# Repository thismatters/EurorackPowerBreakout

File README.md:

Power Breakout
---------------

Ever wanted to prototype a circuit for your Eurorack but didn't have a benchtop power supply for testing? Worry no more! With this small crouton (and an extra long ribbon cable) you can plug your breadboard into your rack as though it were a module.

The crouton includes twin LEDs to show that the 12 volt rails are hot, load smoothing capactiors and resistors. Use a jumper to select between 5 volts and ground on the +12 volt side.

The board can be [ordered directly from OSHpark via this shared project](https://oshpark.com/shared_projects/9Uiejhik).

## Vendors

There are part numbers in the [BOM](vco.csv) for many of the parts (not for basic passives though) at the following vendors:

* [Mouser](https://www.mouser.com): Needs no introduction. Get your ICs from here (or [digikey](https://www.digikey.com)).
* [Tayda Electronics](https://www.taydaelectronics.com/): Good supplier for passive components; audio jacks, and potentiometers. Their audio jacks are slightly smaller than the thonkiconn from thonk.
* [Thonk](https://www.thonk.co.uk/): The only place I've found tempco resistors for sale! You're looking for the 1k resistor, their store doesn't support part number searches.
* [Love My Switches](https://lovemyswitches.com/): Has [really good knobs](https://lovemyswitches.com/anodized-aluminum-knob-the-lo-fi-1-4-smooth-shaft-12-5mm-od/) to go on those potentiometers!
* [OSHPark](https://oshpark.com/): Fast and (relatively) cheap PCB manufacturer. [The V1 circuit](https://oshpark.com/shared_projects/N1VjtYdp) works well, but you'll have to file down the toggle switch legs to fit the tiny through holes on the board.

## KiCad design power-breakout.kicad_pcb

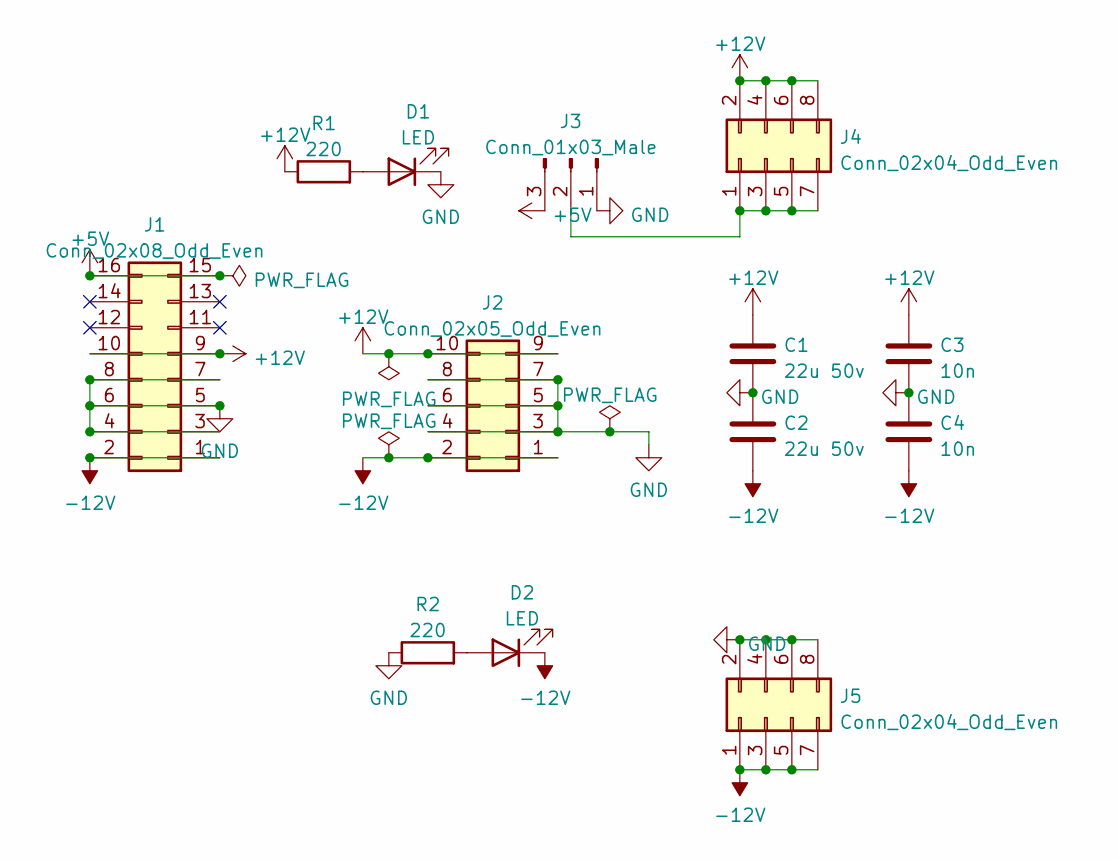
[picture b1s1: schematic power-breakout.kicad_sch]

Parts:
C1, C2: 22u 50v; CP_Radial_D5.0mm_P2.50mm
C3, C4: 10n; C_0805_2012Metric
D1, D2: LED; LED_D5.0mm
J1: Conn_02x08_Odd_Even; PinHeader_2x08_P2.54mm_Vertical
J2: Conn_02x05_Odd_Even; PinHeader_2x05_P2.54mm_Vertical
J3: Conn_01x03_Male; PinHeader_1x03_P2.54mm_Vertical
J4, J5: Conn_02x04_Odd_Even; PinHeader_2x04_P2.54mm_Vertical
R1, R2: 220; R_Axial_DIN0207_L6.3mm_D2.5mm_P2.54mm_Vertical

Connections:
+5V: J1.15, J1.16, J3.3
+12V: C1.1, C3.1, J1.9, J1.10, J2.9, J2.10, J4.2, J4.4, J4.6, J4.8, R1.1
-12V: C2.2, C4.2, D2.1 (K), J1.1, J1.2, J2.1, J2.2, J5.1, J5.3, J5.5, J5.7
GND: C1.2, C2.1, C3.2, C4.1, D1.1 (K), J1.3, J1.4, J1.5, J1.6, J1.7, J1.8, J2.3, J2.4, J2.5, J2.6, J2.7, J2.8, J3.1, J5.2, J5.4, J5.6, J5.8, R2.1
unnamed: D1.2 (A), R1.2
unnamed: D2.2 (A), R2.2
unnamed: J3.2, J4.1, J4.3, J4.5, J4.7

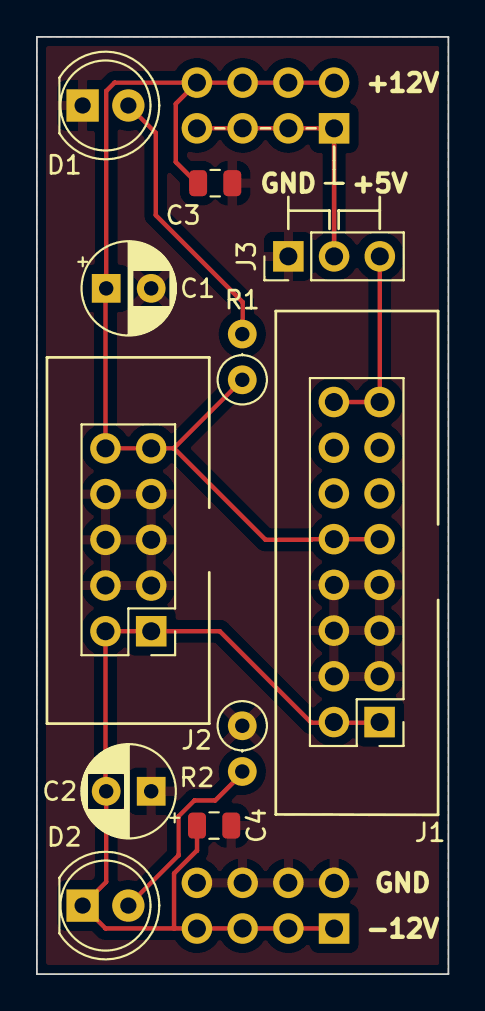
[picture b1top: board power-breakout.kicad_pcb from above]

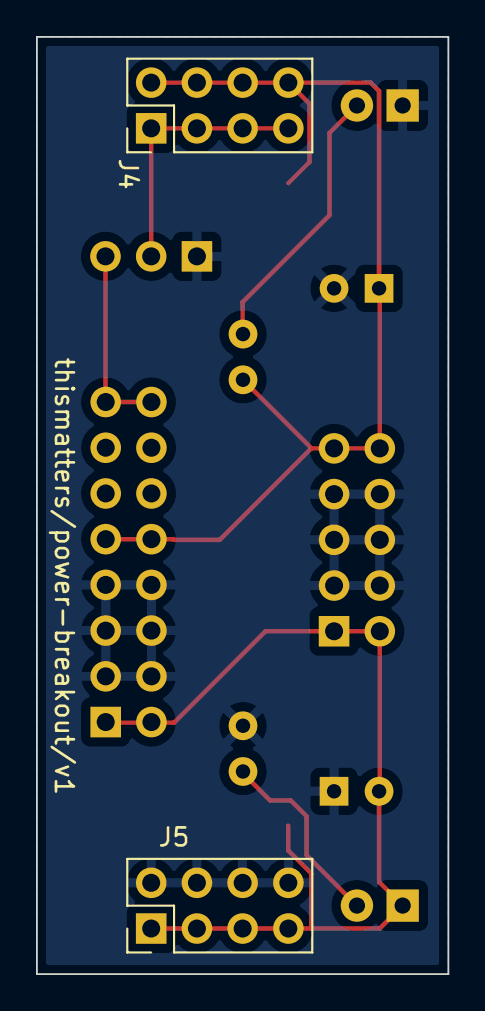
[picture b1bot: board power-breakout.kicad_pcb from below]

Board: 2 copper layers, 22.9 x 52.1 mm, 13 parts (2 on the bottom side), 7 nets.

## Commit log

2024-01-10 adding BoM
2024-01-10 more words
2024-01-10 and xml too
